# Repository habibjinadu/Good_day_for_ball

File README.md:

# Good-Day-for-Ball
Micropython Code for ESP8266 Wemos D1 Mini

This project uses a Wemos D1 Mini, Weather API and an LCD screen to tell you whether it is a good day to play basketball!

Follow the youtube link to view the demo: https://youtu.be/oxwWEuPab40

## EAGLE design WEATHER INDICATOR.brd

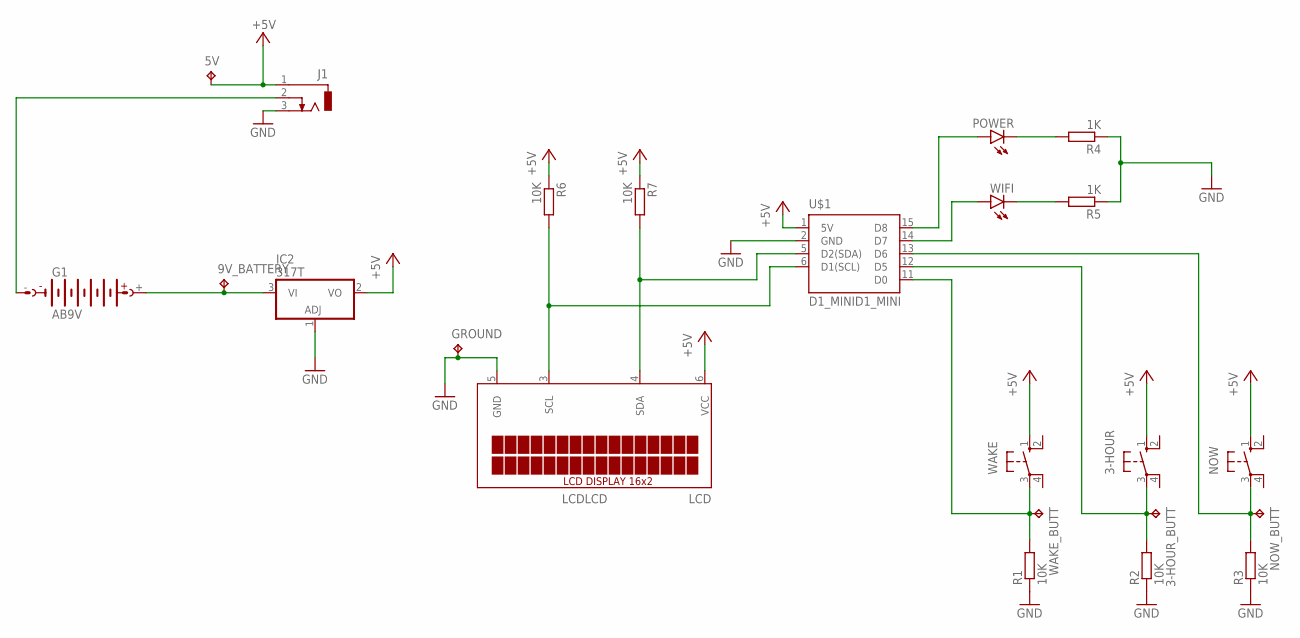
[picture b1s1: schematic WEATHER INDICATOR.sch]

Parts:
3-HOUR: 10-XX; B3F-10XX
3-HOUR_BUTT, 5V, 9V_BATTERY: TPB1,27; B1,27
G1: AB9V
GROUND: TPB1,27; B1,27
IC2: 317T; TO220H
J1: DCJ0303
LCD: LCDLCD; HDRV6W64P254_1X6_1016X508X838B
NOW: 10-XX; B3F-10XX
NOW_BUTT: TPB1,27; B1,27
POWER: LED3MM
R1, R2, R3, R6, R7: 10K; 0204/7
R4, R5: 1K; 0204/7
U$1: D1_MINID1_MINI; DIP2540W53P254L3556H508Q16B
WAKE: 10-XX; B3F-10XX
WAKE_BUTT: TPB1,27; B1,27
WIFI: LED3MM

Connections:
+5V: 3-HOUR.1 (S), 5V.TP, IC2.2 (VO), J1.1, LCD.6 (VCC), NOW.1 (S), R6.1, R7.1, U$1.1 (5V), WAKE.1 (S)
GND: GROUND.TP, IC2.1 (ADJ), J1.3, LCD.5 (GND), R1.1, R2.1, R3.1, R4.1, R5.1, U$1.2 (GND)
unnamed: LCD.4 (SDA), R7.2, U$1.5 (D2(SDA))
unnamed: 9V_BATTERY.TP, G1.+, IC2.3 (VI)
unnamed: G1.-, J1.2
unnamed: LCD.3 (SCL), R6.2, U$1.6 (D1(SCL))
unnamed: 3-HOUR.3, 3-HOUR_BUTT.TP, R2.2, U$1.12 (D5)
unnamed: NOW.3, NOW_BUTT.TP, R3.2, U$1.13 (D6)
unnamed: POWER.K (C), R4.2
unnamed: R5.2, WIFI.K (C)
unnamed: POWER.A, U$1.15 (D8)
unnamed: U$1.14 (D7), WIFI.A
unnamed: R1.2, U$1.11 (D0), WAKE.3, WAKE_BUTT.TP

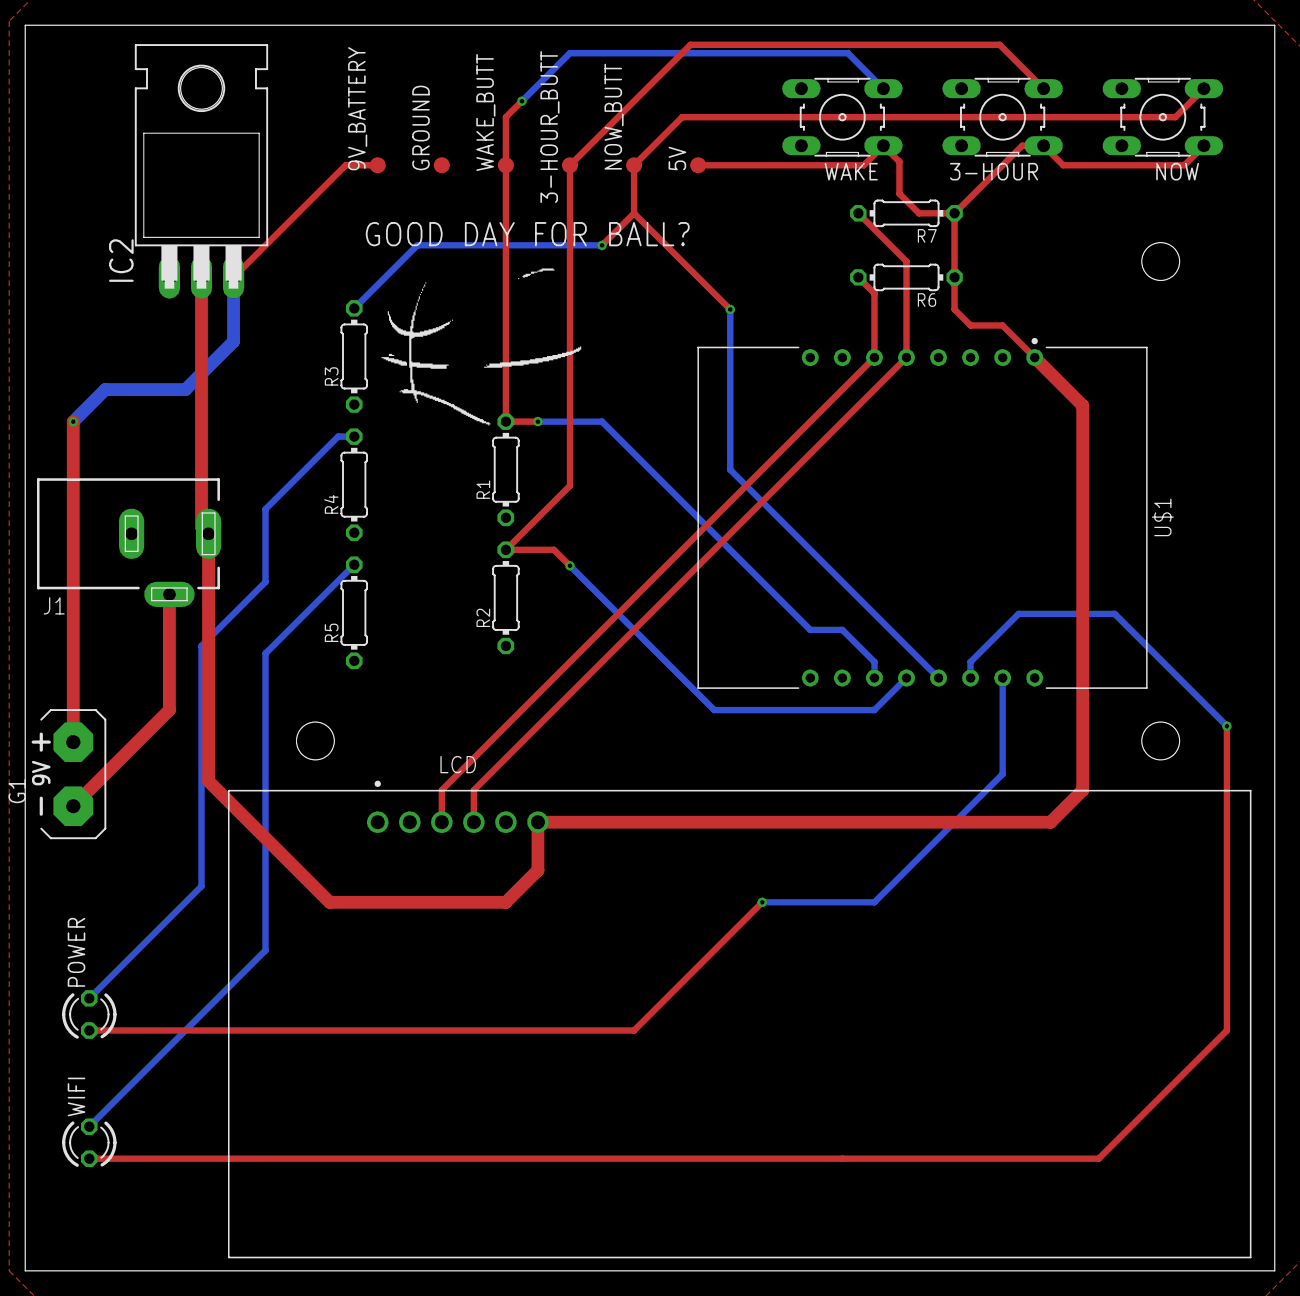
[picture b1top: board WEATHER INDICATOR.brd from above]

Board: 2 copper layers, 99.0 x 98.7 mm, 23 parts (0 on the bottom side), 13 nets.

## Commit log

2020-12-21 improved wifi connection process
2020-12-21 added pushbutton functionality to update the display
2020-12-24 fixed wifi connectivity issue
2020-12-24 added wi-fi connected indicator throuigh red led
2020-12-24 changed the location of interest from Edmonotn to Calgary
